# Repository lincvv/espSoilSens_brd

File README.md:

# esp32 Soil Sensor

**soil moisture measurement - esp32 control**

[_source code from Adafruit for ATSAMD10D14A(I2C sensor)_](https://github.com/adafruit/seesaw)

[_Example User code_](https://github.com/lincvv/Example_ESPSoilSens)

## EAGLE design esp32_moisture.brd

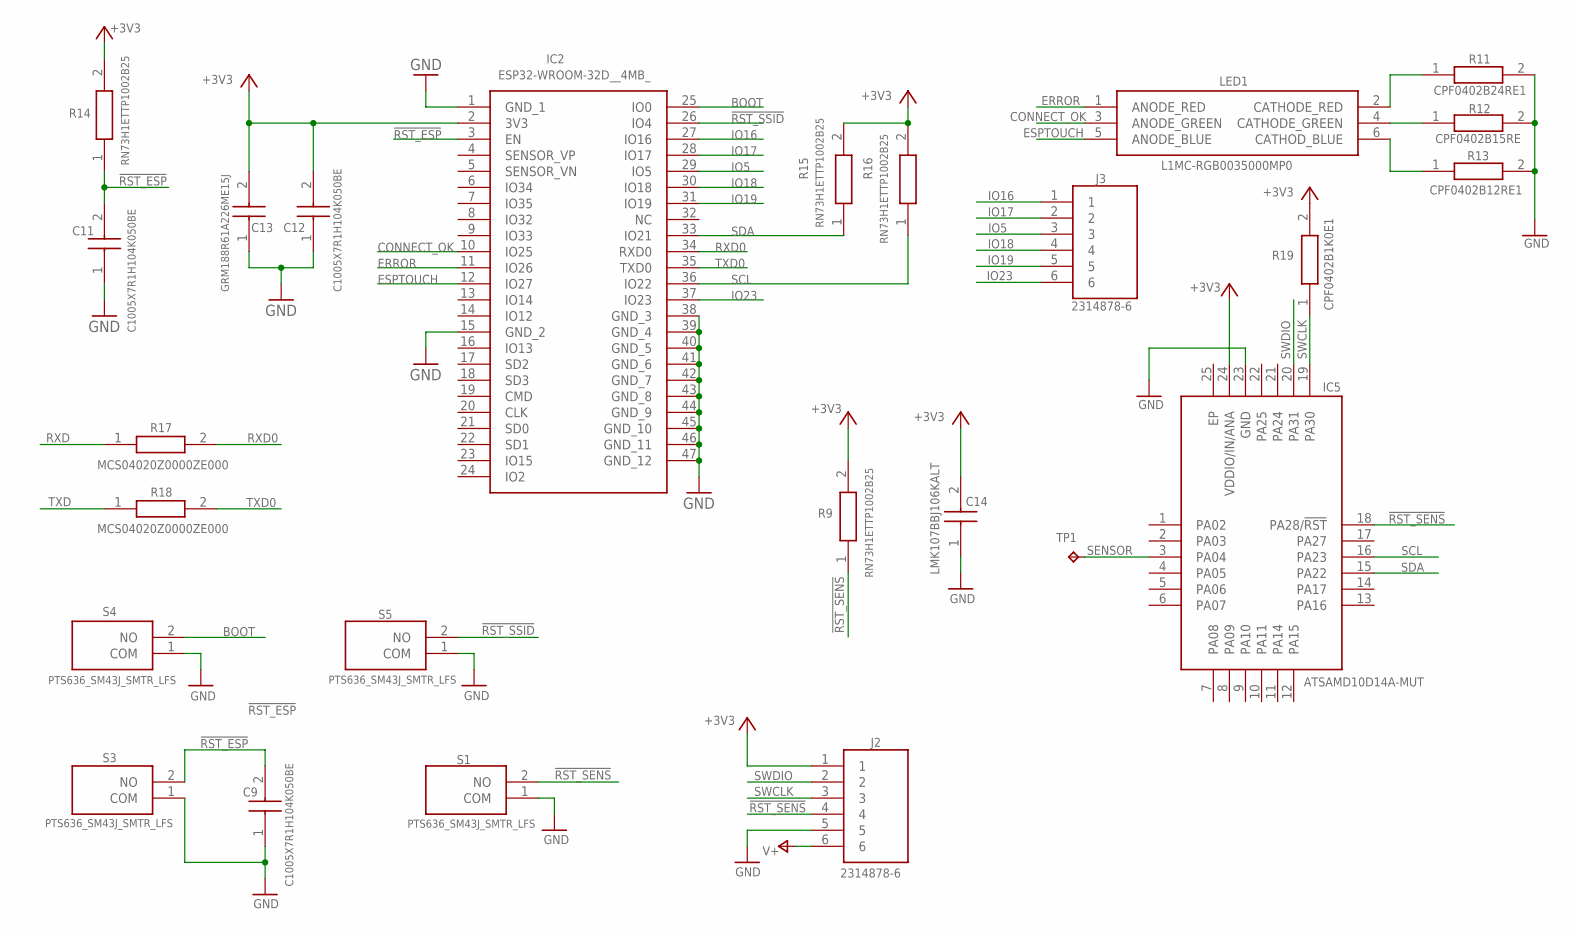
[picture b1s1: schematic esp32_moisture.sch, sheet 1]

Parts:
C9, C11, C12: C1005X7R1H104K050BE; CAPC1005X55N
C13: GRM188R61A226ME15J; CAPC1608X90N
C14: LMK107BBJ106KALT; CAPC1608X100N
IC2: ESP32-WROOM-32D__4MB_; ESP32WROOM32D4MB
IC5: ATSAMD10D14A-MUT; QFN50P400X400X90-25N
J2, J3: 2314878-6; RHDR6W40P0X200_1X6_1200X210X45
LED1: L1MC-RGB0035000MP0; L1MCRGB0035000MP0
R9, R14, R15, R16: RN73H1ETTP1002B25; RESC1005X40N
R11: CPF0402B24RE1; RESC1005X35N
R12: CPF0402B15RE; RESC1005X35N
R13: CPF0402B12RE1; RESC1005X35N
R17, R18: MCS04020Z0000ZE000; RESC1005X37N
R19: CPF0402B1K0E1; RESC1005X35N
S1, S3, S4, S5: PTS636_SM43J_SMTR_LFS; PTS636SM43JSMTRLFS
TP1: TPTP15R; TP15R

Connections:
!RST_ESP: C9.2, C11.2, IC2.3 (EN), R14.1, S3.2 (NO); also elsewhere on the board
!RST_SENS: IC5.18 (PA28/!RST), J2.4, R9.1, S1.2 (NO)
!RST_SSID: IC2.26 (IO4), S5.2 (NO)
+3V3: C12.2, C13.2, C14.2, IC2.2 (3V3), IC5.24 (VDDIO/IN/ANA), J2.1, R9.2, R14.2, R15.2, R16.2, R19.2; also elsewhere on the board
BOOT: IC2.25 (IO0), S4.2 (NO); also elsewhere on the board
CONNECT_OK: IC2.10 (IO25), LED1.3 (ANODE_GREEN)
ERROR: IC2.11 (IO26), LED1.1 (ANODE_RED)
ESPTOUCH: IC2.12 (IO27), LED1.5 (ANODE_BLUE)
GND: C9.1, C11.1, C12.1, C13.1, C14.1, IC2.1 (GND_1), IC2.15 (GND_2), IC2.38 (GND_3), IC2.39 (GND_4), IC2.40 (GND_5), IC2.41 (GND_6), IC2.42 (GND_7), IC2.43 (GND_8), IC2.44 (GND_9), IC2.45 (GND_10), IC2.46 (GND_11), IC2.47 (GND_12), IC5.23 (GND), J2.5, R11.2, R12.2, R13.2, S1.1 (COM), S3.1 (COM), S4.1 (COM), S5.1 (COM); also elsewhere on the board
IO5: IC2.29 (IO5), J3.3
IO16: IC2.27 (IO16), J3.1
IO17: IC2.28 (IO17), J3.2
IO18: IC2.30 (IO18), J3.4
IO19: IC2.31 (IO19), J3.5
IO23: IC2.37 (IO23), J3.6
unnamed: LED1.4 (CATHODE_GREEN), R12.1
unnamed: LED1.2 (CATHODE_RED), R11.1
unnamed: LED1.6 (CATHOD_BLUE), R13.1
RXD: R17.1; also elsewhere on the board
RXD0: IC2.34 (RXD0), R17.2
SCL: IC2.36 (IO22), IC5.16 (PA23), R16.1
SDA: IC2.33 (IO21), IC5.15 (PA22), R15.1
SENSOR: IC5.3 (PA04), TP1.TP
SWCLK: IC5.19 (PA30), J2.3, R19.1
SWDIO: IC5.20 (PA31), J2.2
TXD: R18.1; also elsewhere on the board
TXD0: IC2.35 (TXD0), R18.2
V+: J2.6; also elsewhere on the board

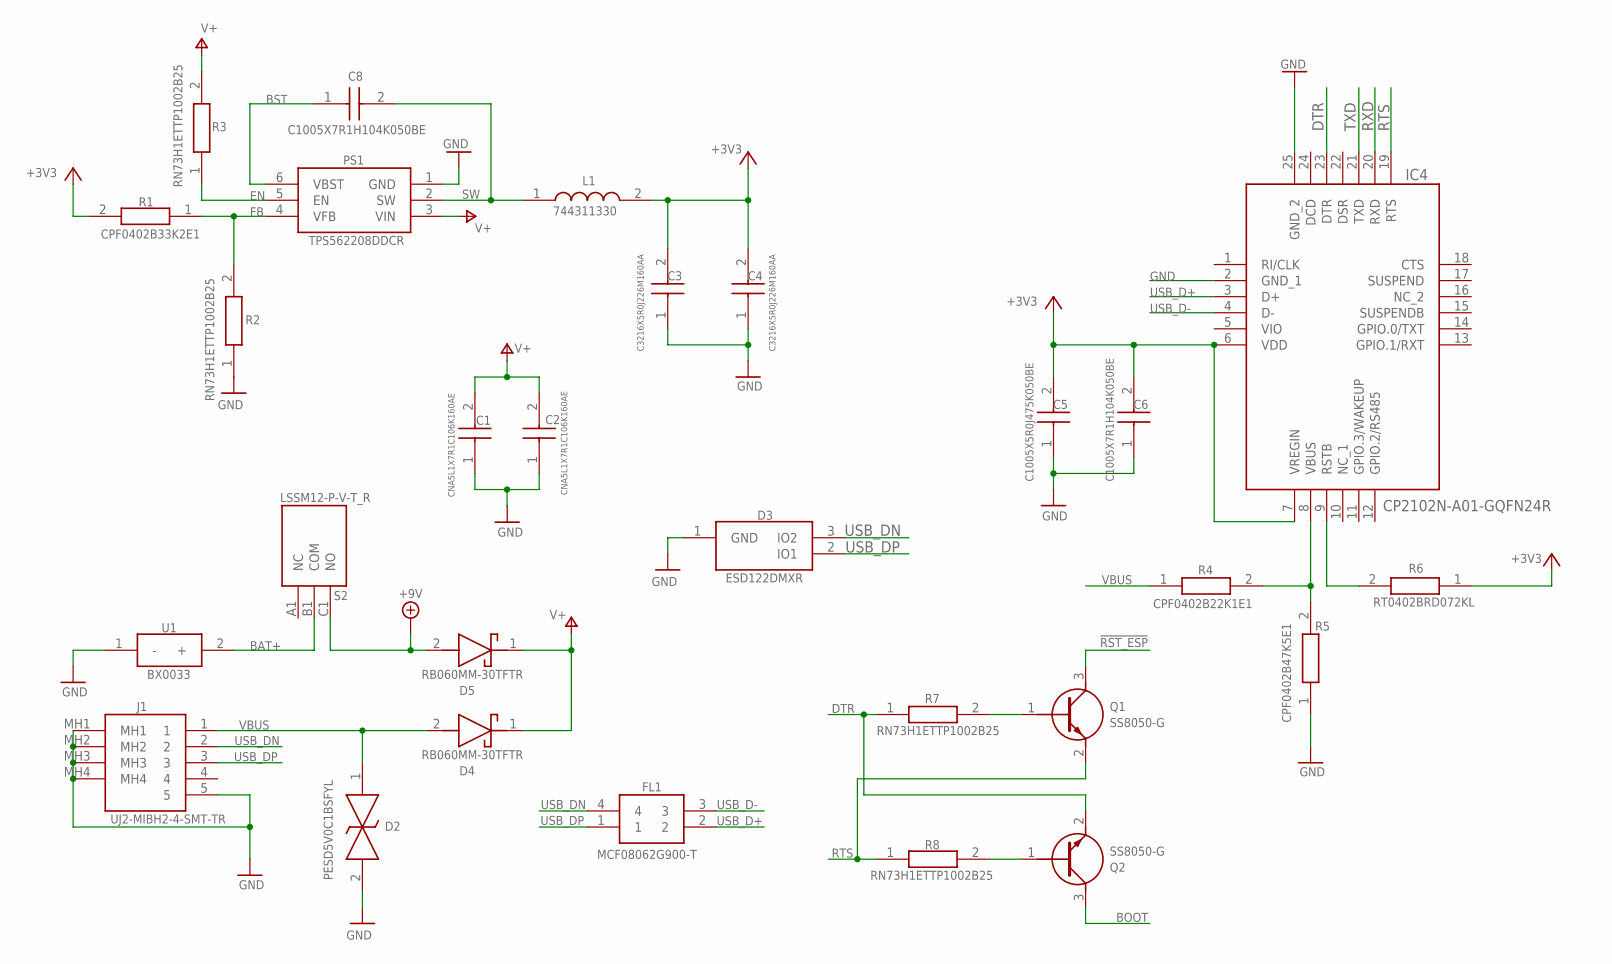
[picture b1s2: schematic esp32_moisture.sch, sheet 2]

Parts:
C1, C2: CNA5L1X7R1C106K160AE; CAPC3216X180N
C3, C4: C3216X5R0J226M160AA; CAPC3216X180N
C5: C1005X5R0J475K050BE; CAPC1005X55N
C6, C8: C1005X7R1H104K050BE; CAPC1005X55N
D2: PESD5V0C1BSFYL; PESD5V0S1USF315
D3: ESD122DMXR; DMX0003A
D4, D5: RB060MM-30TFTR; SODFL3516X90N
FL1: MCF08062G900-T; MCF08062G900T
IC4: CP2102N-A01-GQFN24R; QFN50P400X400X80-25N
J1: UJ2-MIBH2-4-SMT-TR; UJ2MIBH24SMTTR
L1: 744311330; WE-HCI_7030/7040/705023
PS1: TPS562208DDCR; SOT95P280X110-6N
Q1, Q2: SS8050-G; SOT95P240X115-3N
R1: CPF0402B33K2E1; RESC1005X35N
R2, R3, R7, R8: RN73H1ETTP1002B25; RESC1005X40N
R4: CPF0402B22K1E1; RESC1005X35N
R5: CPF0402B47K5E1; RESC1005X35N
R6: RT0402BRD072KL; RESC1005X35N
S2: LSSM12-P-V-T_R; LSSM12PVTR
U1: BX0033

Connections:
!RST_ESP: Q1.3 (C); also elsewhere on the board
+3V3: C3.2, C4.2, C5.2, C6.2, IC4.6 (VDD), IC4.7 (VREGIN), L1.2, R1.2, R6.1; also elsewhere on the board
+9V: D5.2 (A), S2.C1 (NO)
BAT+: S2.B1 (COM), U1.2 (+)
BOOT: Q2.3 (C); also elsewhere on the board
BST: C8.1, PS1.6 (VBST)
DTR: IC4.23 (DTR), Q2.2 (E), R7.1
EN: PS1.5 (EN), R3.1
FB: PS1.4 (VFB), R1.1, R2.2
GND: C1.1, C2.1, C3.1, C4.1, C5.1, C6.1, D2.2, D3.1 (GND), IC4.2 (GND_1), IC4.25 (GND_2), J1.5, J1.MH1, J1.MH2, J1.MH3, J1.MH4, PS1.1 (GND), R2.1, R5.1, U1.1 (-); also elsewhere on the board
unnamed: IC4.9 (RSTB), R6.2
unnamed: Q1.1 (B), R7.2
unnamed: Q2.1 (B), R8.2
unnamed: IC4.8 (VBUS), R4.2, R5.2
RTS: IC4.19 (RTS), Q1.2 (E), R8.1
RXD: IC4.20 (RXD); also elsewhere on the board
SW: C8.2, L1.1, PS1.2 (SW)
TXD: IC4.21 (TXD); also elsewhere on the board
USB_D+: FL1.2, IC4.3 (D+)
USB_D-: FL1.3, IC4.4 (D-)
USB_DN: D3.3 (IO2), FL1.4, J1.2
USB_DP: D3.2 (IO1), FL1.1, J1.3
V+: C1.2, C2.2, D4.1 (K), D5.1 (K), PS1.3 (VIN), R3.2; also elsewhere on the board
VBUS: D2.1, D4.2 (A), J1.1, R4.1

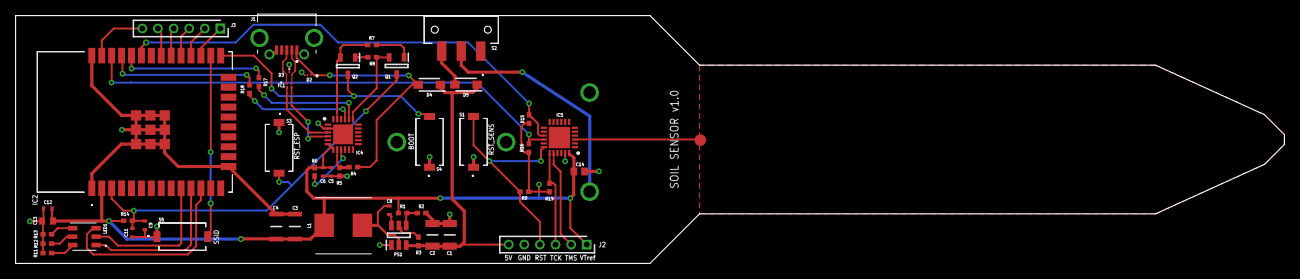
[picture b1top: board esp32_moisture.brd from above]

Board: 2 copper layers, 162.6 x 31.8 mm, 53 parts (1 on the bottom side), 45 nets.

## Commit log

2021-03-13 init
2021-03-13 feath(.brd, .sch)
